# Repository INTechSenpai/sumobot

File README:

Projet Sumobot 2015-2016 du club INTech

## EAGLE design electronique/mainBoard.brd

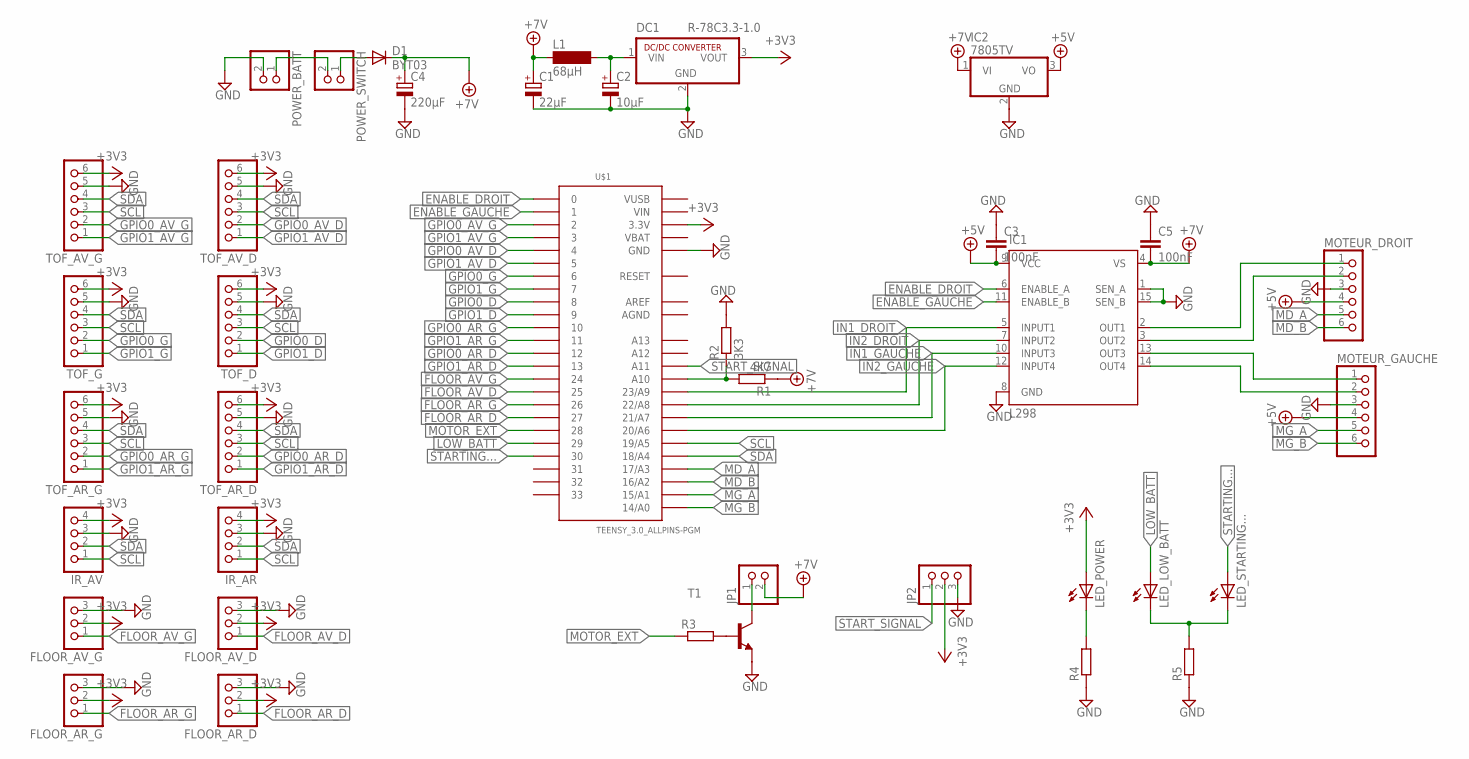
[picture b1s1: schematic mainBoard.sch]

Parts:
C1: 22µF; E2,5-6E
C2: 10µF; E2,5-6E
C3, C5: 100nF; C050-024X044
C4: 220µF; E2,5-7
D1: BYT03; DO27-15
DC1: R-78C3.3-1.0; SIP3
FLOOR_AR_D: PINHD-1X3; 1X03
FLOOR_AR_G: PINHD-1X3; 1X03
FLOOR_AV_D: PINHD-1X3; 1X03
FLOOR_AV_G: PINHD-1X3; 1X03
IC1: L298; MULTIWATT-15
IC2: 7805TV; TO220V
IR_AR: PINHD-1X4; 1X04
IR_AV: PINHD-1X4; 1X04
JP1: PINHD-1X2; 1X02
JP2: PINHD-1X3; 1X03
L1: 68µH; BS11
LED_LOW_BATT: LED3MM
LED_POWER: LED3MM
LED_STARTING...: LED3MM
MOTEUR_DROIT: PINHD-1X6; 1X06
MOTEUR_GAUCHE: PINHD-1X6; 1X06
POWER_BATT: PINHD-1X2; 1X02
POWER_SWITCH: PINHD-1X2; 1X02
R1: 4K7; 0204/7
R2: 3K3; 0204/7
R3, R4: R-EU_0204/7; 0204/7
R5: R-EU_0207/2V; 0207/2V
T1: 2N4124-NPN-TO92-CBE; TO92-CBE
TOF_AR_D: PINHD-1X6; 1X06
TOF_AR_G: PINHD-1X6; 1X06
TOF_AV_D: PINHD-1X6; 1X06
TOF_AV_G: PINHD-1X6; 1X06
TOF_D: PINHD-1X6; 1X06
TOF_G: PINHD-1X6; 1X06
U$1: TEENSY_3.0_ALLPINS-PGM

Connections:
+3V3: DC1.3 (VOUT), FLOOR_AR_D.2, FLOOR_AR_G.2, FLOOR_AV_D.2, FLOOR_AV_G.2, IR_AR.4, IR_AV.4, JP2.2, LED_POWER.A, TOF_AR_D.6, TOF_AR_G.6, TOF_AV_D.6, TOF_AV_G.6, TOF_D.6, TOF_G.6, U$1.3.3V, U$1.3.3V1 (3.3V), U$1.3.3V2 (3.3V)
+5V: C3.2, IC1.9 (VCC), IC2.3 (VO), MOTEUR_DROIT.4, MOTEUR_GAUCHE.4
+7V: C1.+, C4.+, C5.2, D1.C, IC1.4 (VS), IC2.1 (VI), JP1.2, L1.1, R1.1
AGND: U$1.AGND
AREF: U$1.AREF
ENABLE_DROIT: IC1.6 (ENABLE_A), U$1.0
ENABLE_GAUCHE: IC1.11 (ENABLE_B), U$1.1
FLOOR_AR_D: FLOOR_AR_D.1, U$1.27
FLOOR_AR_G: FLOOR_AR_G.1, U$1.26
FLOOR_AV_D: FLOOR_AV_D.1, U$1.25
FLOOR_AV_G: FLOOR_AV_G.1, U$1.24
GND: C1.-, C2.-, C3.1, C4.-, C5.1, DC1.2 (GND), FLOOR_AR_D.3, FLOOR_AR_G.3, FLOOR_AV_D.3, FLOOR_AV_G.3, IC1.1 (SEN_A), IC1.8 (GND), IC1.15 (SEN_B), IC2.2 (GND), IR_AR.3, IR_AV.3, JP2.3, MOTEUR_DROIT.3, MOTEUR_GAUCHE.3, POWER_BATT.2, R2.2, R4.1, R5.1, T1.E, TOF_AR_D.5, TOF_AR_G.5, TOF_AV_D.5, TOF_AV_G.5, TOF_D.5, TOF_G.5, U$1.GND, U$1.GND1 (GND), U$1.GND2 (GND)
GPIO0_AR_D: TOF_AR_D.2, U$1.12
GPIO0_AR_G: TOF_AR_G.2, U$1.10
GPIO0_AV_D: TOF_AV_D.2, U$1.4
GPIO0_AV_G: TOF_AV_G.2, U$1.2
GPIO0_D: TOF_D.2, U$1.8
GPIO0_G: TOF_G.2, U$1.6
GPIO1_AR_D: TOF_AR_D.1, U$1.13
GPIO1_AR_G: TOF_AR_G.1, U$1.11
GPIO1_AV_D: TOF_AV_D.1, U$1.5
GPIO1_AV_G: TOF_AV_G.1, U$1.3
GPIO1_D: TOF_D.1, U$1.9
GPIO1_G: TOF_G.1, U$1.7
IN1_DROIT: IC1.5 (INPUT1), U$1.23/A9
IN1_GAUCHE: IC1.10 (INPUT3), U$1.21/A7
IN2_DROIT: IC1.7 (INPUT2), U$1.22/A8
IN2_GAUCHE: IC1.12 (INPUT4), U$1.20/A6
LOW_BATT: LED_LOW_BATT.A, U$1.29
MD_A: MOTEUR_DROIT.5, U$1.17/A3
MD_B: MOTEUR_DROIT.6, U$1.16/A2
MD_OUT_A: IC1.2 (OUT1), MOTEUR_DROIT.1
MD_OUT_B: IC1.3 (OUT2), MOTEUR_DROIT.2
MG_A: MOTEUR_GAUCHE.5, U$1.15/A1
MG_B: MOTEUR_GAUCHE.6, U$1.14/A0
MG_OUT_A: IC1.13 (OUT3), MOTEUR_GAUCHE.1
MG_OUT_B: IC1.14 (OUT4), MOTEUR_GAUCHE.2
MOTOR_EXT: R3.1, U$1.28
unnamed: R3.2, T1.B
unnamed: C2.+, DC1.1 (VIN), L1.2
unnamed: JP1.1, T1.C
unnamed: POWER_BATT.1, POWER_SWITCH.2
unnamed: D1.A, POWER_SWITCH.1
unnamed: LED_POWER.K (C), R4.2
unnamed: R1.2, R2.1, U$1.A10
unnamed: LED_LOW_BATT.K (C), LED_STARTING....K (C), R5.2
SCL: IR_AR.1, IR_AV.1, TOF_AR_D.3, TOF_AR_G.3, TOF_AV_D.3, TOF_AV_G.3, TOF_D.3, TOF_G.3, U$1.19/A5
SDA: IR_AR.2, IR_AV.2, TOF_AR_D.4, TOF_AR_G.4, TOF_AV_D.4, TOF_AV_G.4, TOF_D.4, TOF_G.4, U$1.18/A4
STARTING...: LED_STARTING....A, U$1.30
START_SIGNAL: JP2.1, U$1.A11
VBAT: U$1.VBAT
VIN: U$1.VIN
VUSB: U$1.VUSB

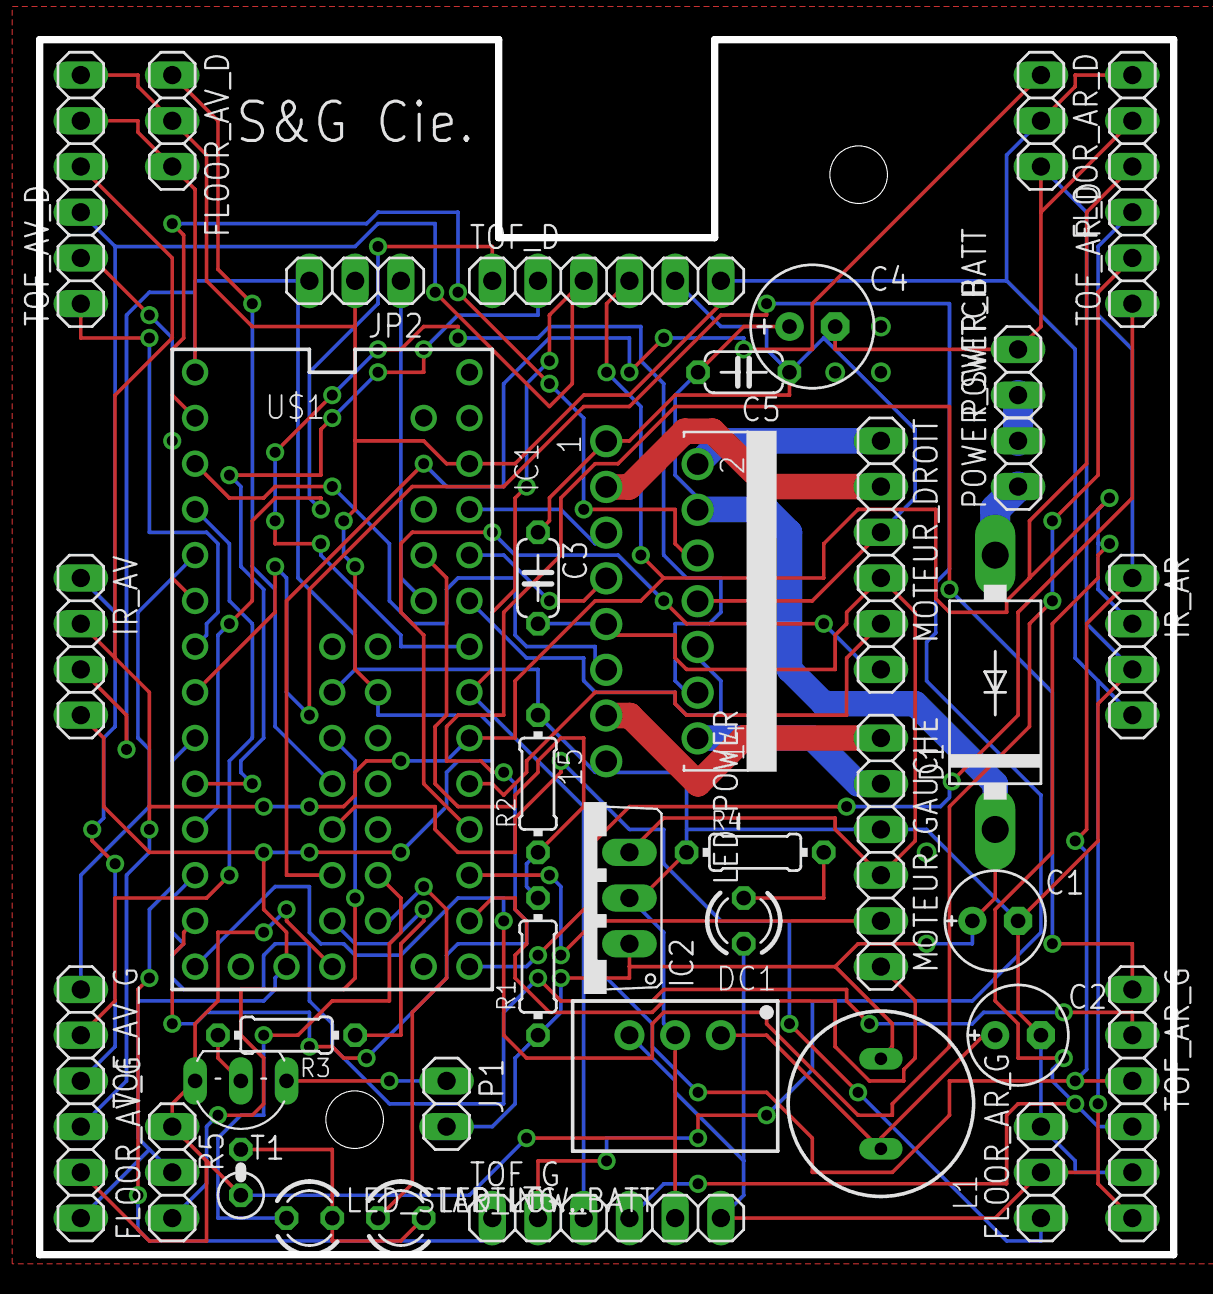
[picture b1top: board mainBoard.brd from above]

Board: 2 copper layers, 63.0 x 67.5 mm, 38 parts (0 on the bottom side), 48 nets.

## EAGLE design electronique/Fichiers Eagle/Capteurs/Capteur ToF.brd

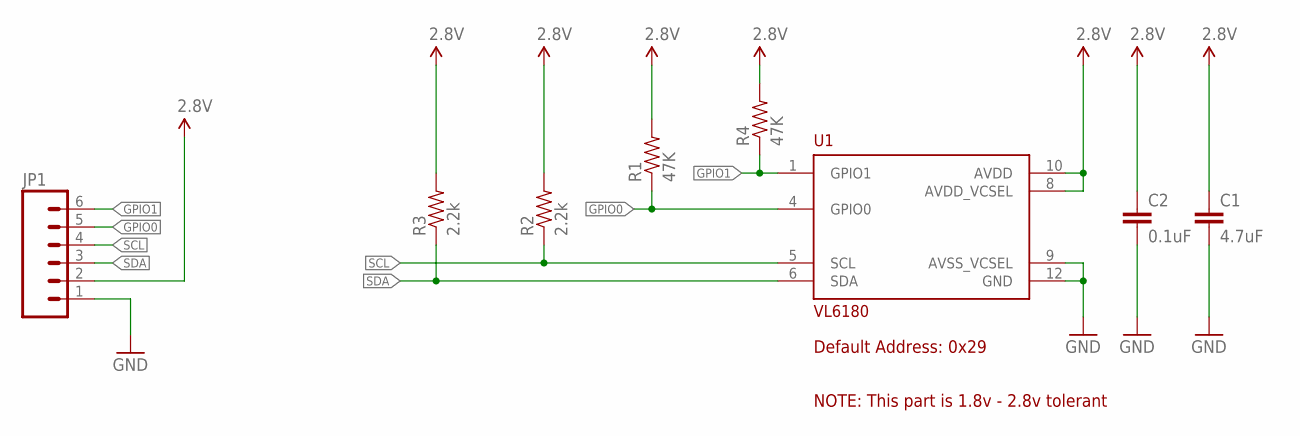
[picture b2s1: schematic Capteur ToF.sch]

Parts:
C1: 4.7uF; 0603-CAP
C2: 0.1uF; 0603-CAP
JP1: M06SIP; 1X06
R1, R4: 47K; 0603-RES
R2, R3: 2.2k; 0603-RES
U1: VL6180

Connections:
2.8V: C1.1, C2.1, JP1.2, R1.2, R2.2, R3.2, R4.2, U1.8 (AVDD_VCSEL), U1.10 (AVDD)
GND: C1.2, C2.2, JP1.1, U1.9 (AVSS_VCSEL), U1.12 (GND)
GPIO0: JP1.5, R1.1, U1.4 (GPIO0)
GPIO1: JP1.6, R4.1, U1.1 (GPIO1)
SCL: JP1.4, R2.1, U1.5 (SCL)
SDA: JP1.3, R3.1, U1.6 (SDA)

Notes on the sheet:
Default Address: 0x29
NOTE: This part is 1.8v - 2.8v tolerant

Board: 2 copper layers, 8 parts (0 on the bottom side), 6 nets, no tracks yet.

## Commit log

2015-12-17 The First Commit
2015-12-19 Ajout du .gitignore
2015-12-19 ajout du dossier electronique
2015-12-22 maj modele 3D + ajout d'un début de circuit electronique
2015-12-26 ajout d'un dÃebut d'UML et d'une description succinte de chacune des classes
2015-12-30 Maj de l'UML
2016-01-23 circuit electronique git status!
2016-01-24 MAJ electronique (final version)
2016-01-26 mecanique : mise a jour de la base du robot
2016-02-06 programmation : ajout du projet Teensy
2016-02-08 ajout du code bas niveau
2016-02-10 ajout d'un algorithme A* qui MARCHE
2016-02-10 MAJ UML + commentaires dans le code bas niveau
2016-02-17 mÃaj Code low level
2016-02-20 control des moteurs OK + controle tension des lipos fonctionnel
2016-02-28 ajout des capteurs ToF dans le code bas niveau
2016-03-04 bases obstacles
2016-03-05 ùAjout de doc + code des capteurs IR
2016-03-06 affinement des classes obstacles
2016-03-07 ajout du code des capteurs noir-blanc
2016-03-07 debut du code du pathfinding pour le robot
2016-03-07 debut du code du pathfinding pour le robot qui compile
2016-03-07 mise a jour de RelativeObstacleMap.h et de Path.h
2016-03-07 ajout des differents noeuds possible dans pathfinding
2016-03-07 maj du fichier path.h pour la compatibilite haut/bas niveau
2016-03-08 capteurs noir/blanc enfin fonctionnels + maj RelativeObstacleMap (changement des types)
2016-03-08 Specification précide de la structure RelativeObstacleMap
2016-03-08 ajout de supports pour les capteurs + doc des emplacements des capteurs
2016-03-08 ajout dans updateMapping
2016-03-08 les vector sont triés
2016-03-09 detection des obstacles
2016-03-09 j'inclue les .h de malcolm
2016-03-09 premiers tests
2016-03-09 gestion bas niveau des capteurs operationnelle pour TOUS les capteurs !
2016-03-10 pathfinding qui evite les ObstacleCercle
2016-03-10 changement sur la vitesse et petits tests
2016-03-10 Gestion de la vitesse de variation des capteurs
2016-03-10 chgt dues aux test
2016-03-10 changement pour la vitesse
2016-03-10 test class Table avec le robot
2016-03-10 changement pour la vitesse 2
2016-03-10 capteurs au sol
2016-03-10 la distance prend en compte l'ecart d'orientation
2016-03-10 all the sensors works... mais pas la table
2016-03-10 verification si le trajet est possible
2016-03-10 petit changement capteurs au sol
2016-03-11 modifs de malcolm
2016-03-11 inclusion des bon .h
2016-03-11 changement capteur aux sol
2016-03-11 debut de la fonction pour sortir un objet Trajectory
2016-03-11 malcolm m'a piquÃe mon pc
2016-03-12 encore ces putains de capteurs au sol
2016-03-12 recupere le type de la trajectoire a la fin
2016-03-12 chgt apres tests capteurs au sol
2016-03-12 Nouveau 'Pathdfinding' plus simple, prend 3 points et ressort une trajectoire
2016-03-13 ajout du compte rendu K6OP
2016-03-14 possibilité de calculer une trajectoire soit a partir de 3 points soit a partir de deux positions en precisant les orientations
2016-03-16 ajout des modulo sur les orientation dans pathfinding
2016-03-16 changements pour CUILLERE
2016-03-16 changements pour les marges de capteurs cotés
2016-03-16 changements pour les commentaires
2016-03-16 maj MotionControlSysyem
2016-03-16 debut de la classe robot et strategy
2016-03-17 ajout d'une strategie possible pour le robot
2016-03-17 changement coherence
2016-03-17 test numero deux cohernece capteurs
2016-03-17 maj minimes lolilol
2016-03-17 test 3 coherence salete d unsigned
2016-03-17 changements vitesse malcolm
2016-03-18 avancée dans la strategie
2016-03-18 ajout sequence de demarrage permettant de replier le robot
2016-03-18 strategy
2016-03-18 changements non perdu si bord detecter et robot proche de nous
2016-03-18 code de test + maj motioncontrolsystem
2016-03-18 ajout pathfinding robot
2016-03-18 changement repistionnement capteurs au sol
2016-03-18 piti changements
2016-03-18 ajout desengagement en cas de detection de bord
2016-03-18 correction trajectoire courbe
2016-03-18 changment cast et robot
2016-03-18 correction erreurs
2016-03-18 changement prototype du getPosition
2016-03-18 ARTHUR J'AURAIS TA PEAU git status! (met jai corrigé ton bug)
2016-03-18 mise en place de la trajectoire courbe
2016-03-18 petit changement dans pathfinding
2016-03-18 bug tourne sur lui meme capteurs
2016-03-18 test de trajectoire
2016-03-18 pour Sylvain
2016-03-19 tests tests tests[D
2016-03-19 robot qui gagne une fois sur 3
2016-03-19 maj du detecteur de bords
2016-03-19 detection des bords OK
2016-03-19 maj timer desengagement
2016-03-19 final malcolm
2016-03-19 abwabwa
2016-03-19 Code qui gagne tous les match !
2016-03-20 Nettoyage du code apres Sumobot. Ajout d'une structure de test (CUnit) et corrections des problemes de portee des variables
2016-03-24 calculs refaits pour le pathfinding
2016-03-25 modif Obstacle + Table en prÃevision de la nouvelle archi du code
2016-04-11 la fonction pathfinding renvoie une trajectoire, prend en compte les rotations
2016-04-11 The robot is ready to be coded !
2016-04-12 ajout des obstacles
2016-04-14 computePath rajouté
2016-04-14 prend en compte maintenant tous les obstacles
2016-04-14 fonction de détection d'obstacle corrigée
2016-04-16 modification pour prendre en compte le fait que XRadius et YRadius correspondent respectivement à la largeur et la hauteur de l'obstacle rectangle
2016-04-16 Correctifs du motionControlSystem : constantes de conversion tick mm radian + enchainement des mouvements
2016-04-17 ajout detection de cote de table en debut de match
2016-04-17 corrections + interdit les rotations quand le robot est en train de pousser un objet
2016-04-17 Ajout des prototypes de presque toutes les methodes de Robot.h avec leurs specifications
2016-04-18 define estsurordi
2016-04-18 concatenation des trajectoires
2016-04-18 prise en compte du cas ou le pathfinding apparait sur un obstacle non fixe
2016-04-20 ajout debut positionnement d'obtacles
2016-04-20 agrandissement de la taille des obstacles
2016-04-22 ajout de le fonction 'longer bord de table' non testee
2016-04-23 Début de match testé et approuvé. Script 'longe bord de table' en cours de réglages
2016-04-23 le script de fermeture des deux portes est fonctionnel et fiable du côté violet, fonctionnel du côté vert
2016-04-23 gestion plus intelligente des contraintes d'arrivées
2016-04-25 maj script close doors + progression de la gestiond des obstacles
2016-04-27 détection des obstacles OK (il ne manque plus que l'interprétation gros/petit obstacle)
2016-04-28 detection des obstacles OK git status Motherfucker ! (reste plus qu'à faire l'interprétation pour voir des robots adverses
2016-04-28 correction : la taille de la table était augmentée au lieu de diminuée pour prendre en compte la taille du robot
2016-04-28 suppression d'un rayon de courbure pour le robot ce qui donne de meilleurs résultats
2016-04-29 ajout évitement OVERKILL (qui marche pas, mais je commit pour la beauté des calculs dégeu)
2016-04-29 Evitement OK + script close door = homologation
2016-05-01 script push sand OK côté vert
2016-05-02 robot fonctionnel.
2016-05-02 bon ça marche du côté vert, reste plus qu'à faire l'autre et go for the win !
2016-05-03 dernier commit avant le départ à la coupe
2016-05-04 test fin de match yolo
2017-06-18 commit post-coupe

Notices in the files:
parts and their libraries:
SparkFun-Resistors: Licensing: CC v3.0 Share-Alike You are welcome to use this library for commercial purposes.
